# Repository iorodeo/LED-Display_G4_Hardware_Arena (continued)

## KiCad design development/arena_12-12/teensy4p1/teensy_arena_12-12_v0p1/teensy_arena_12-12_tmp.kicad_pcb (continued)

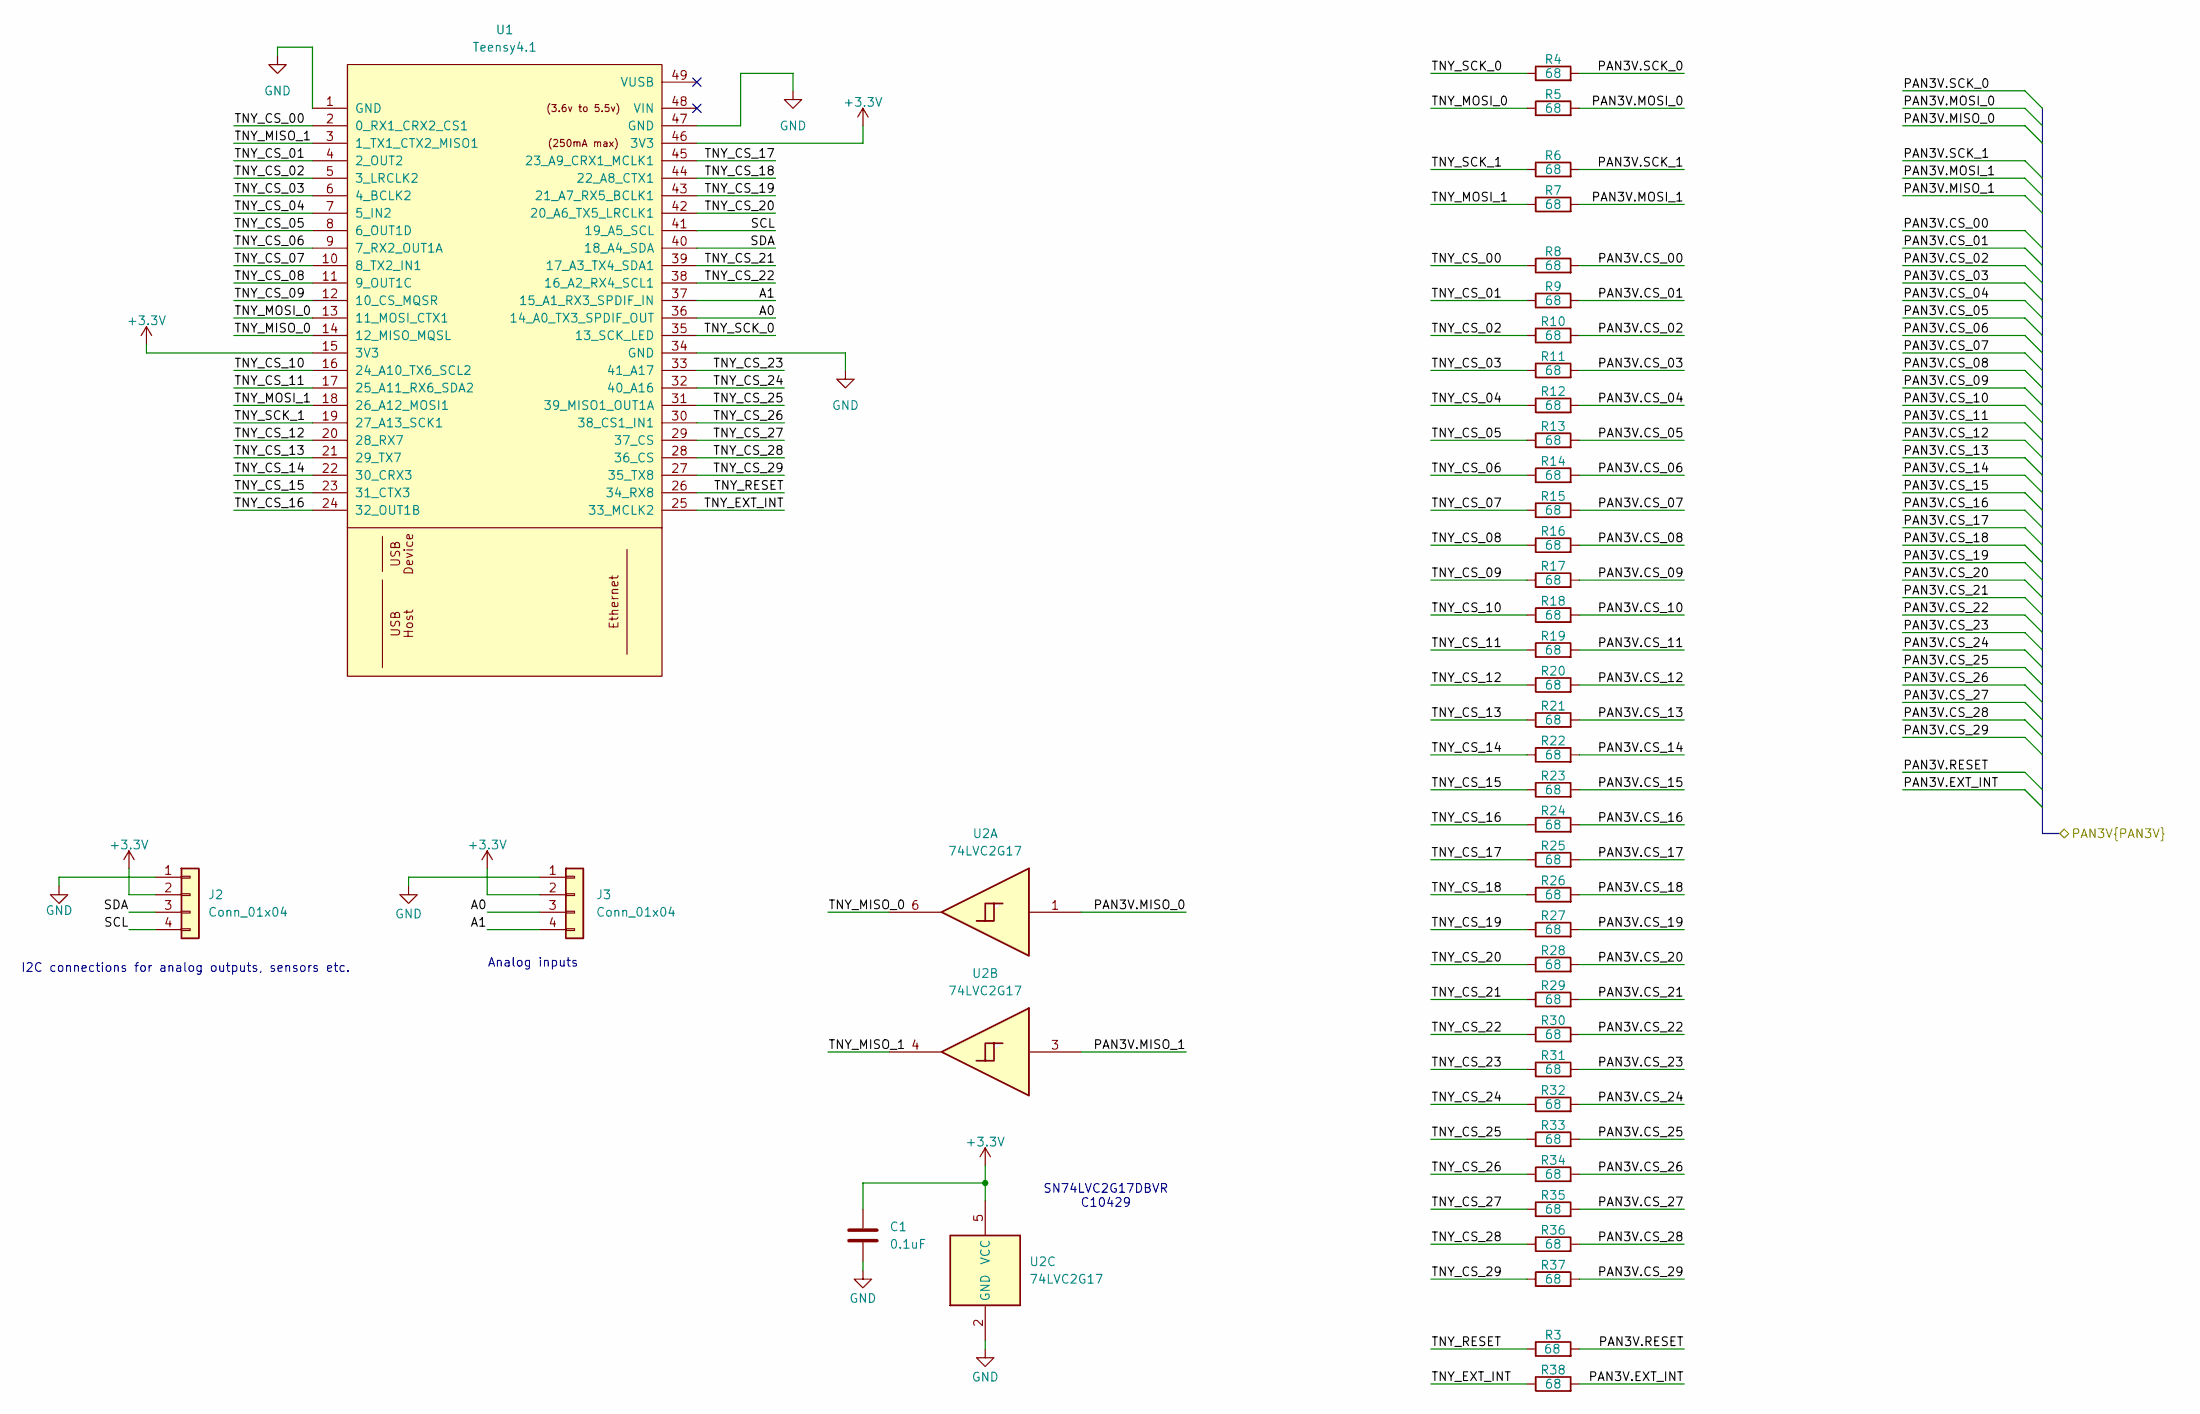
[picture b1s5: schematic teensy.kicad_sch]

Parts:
C1: 0.1uF; C_0402_1005Metric
J2, J3: Conn_01x04; JST_SH_SM04B-SRSS-TB_1x04-1MP_P1.00mm_Horizontal
R3, R4, R5, R6, R7, R8, R9, R10, R11, R12, R13, R14, R15, R16, R17, R18, R19, R20, R21, R22, R23, R24, R25, R26, R27, R28, R29, R30, R31, R32, R33, R34, R35, R36, R37, R38: 68; R_0402_1005Metric
U1: Teensy4.1; Teensy41_outer_only
U2: 74LVC2G17; SOT-23-6

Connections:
+3.3V: C1.1, J2.2, J3.2, U1.15 (3V3), U1.46 (3V3), U2.5 (VCC); also elsewhere on the board
/Level Shifters/PAN3V.CS_00: R8.2; also elsewhere on the board
/Level Shifters/PAN3V.CS_01: R9.2; also elsewhere on the board
/Level Shifters/PAN3V.CS_02: R10.2; also elsewhere on the board
/Level Shifters/PAN3V.CS_03: R11.2; also elsewhere on the board
/Level Shifters/PAN3V.CS_04: R12.2; also elsewhere on the board
/Level Shifters/PAN3V.CS_05: R13.2; also elsewhere on the board
/Level Shifters/PAN3V.CS_06: R14.2; also elsewhere on the board
/Level Shifters/PAN3V.CS_07: R15.2; also elsewhere on the board
/Level Shifters/PAN3V.CS_08: R16.2; also elsewhere on the board
/Level Shifters/PAN3V.CS_09: R17.2; also elsewhere on the board
/Level Shifters/PAN3V.CS_10: R18.2; also elsewhere on the board
/Level Shifters/PAN3V.CS_11: R19.2; also elsewhere on the board
/Level Shifters/PAN3V.CS_12: R20.2; also elsewhere on the board
/Level Shifters/PAN3V.CS_13: R21.2; also elsewhere on the board
/Level Shifters/PAN3V.CS_14: R22.2; also elsewhere on the board
/Level Shifters/PAN3V.CS_15: R23.2; also elsewhere on the board
/Level Shifters/PAN3V.CS_16: R24.2; also elsewhere on the board
/Level Shifters/PAN3V.CS_17: R25.2; also elsewhere on the board
/Level Shifters/PAN3V.CS_18: R26.2; also elsewhere on the board
/Level Shifters/PAN3V.CS_19: R27.2; also elsewhere on the board
/Level Shifters/PAN3V.CS_20: R28.2; also elsewhere on the board
/Level Shifters/PAN3V.CS_21: R29.2; also elsewhere on the board
/Level Shifters/PAN3V.CS_22: R30.2; also elsewhere on the board
/Level Shifters/PAN3V.CS_23: R31.2; also elsewhere on the board
/Level Shifters/PAN3V.CS_24: R32.2; also elsewhere on the board
/Level Shifters/PAN3V.CS_25: R33.2; also elsewhere on the board
/Level Shifters/PAN3V.CS_26: R34.2; also elsewhere on the board
/Level Shifters/PAN3V.CS_27: R35.2; also elsewhere on the board
/Level Shifters/PAN3V.CS_28: R36.2; also elsewhere on the board
/Level Shifters/PAN3V.CS_29: R37.2; also elsewhere on the board
/Level Shifters/PAN3V.EXT_INT: R38.2; also elsewhere on the board
/Level Shifters/PAN3V.MISO_0: U2.1; also elsewhere on the board
/Level Shifters/PAN3V.MISO_1: U2.3; also elsewhere on the board
/Level Shifters/PAN3V.MOSI_0: R5.2; also elsewhere on the board
/Level Shifters/PAN3V.MOSI_1: R7.2; also elsewhere on the board
/Level Shifters/PAN3V.RESET: R3.2; also elsewhere on the board
/Level Shifters/PAN3V.SCK_0: R4.2; also elsewhere on the board
/Level Shifters/PAN3V.SCK_1: R6.2; also elsewhere on the board
/Teensy/A0: J3.3, U1.36 (14_A0_TX3_SPDIF_OUT)
/Teensy/A1: J3.4, U1.37 (15_A1_RX3_SPDIF_IN)
/Teensy/SCL: J2.4, U1.41 (19_A5_SCL)
/Teensy/SDA: J2.3, U1.40 (18_A4_SDA)
/Teensy/TNY_CS_00: R8.1, U1.2 (0_RX1_CRX2_CS1)
/Teensy/TNY_CS_01: R9.1, U1.4 (2_OUT2)
/Teensy/TNY_CS_02: R10.1, U1.5 (3_LRCLK2)
/Teensy/TNY_CS_03: R11.1, U1.6 (4_BCLK2)
/Teensy/TNY_CS_04: R12.1, U1.7 (5_IN2)
/Teensy/TNY_CS_05: R13.1, U1.8 (6_OUT1D)
/Teensy/TNY_CS_06: R14.1, U1.9 (7_RX2_OUT1A)
/Teensy/TNY_CS_07: R15.1, U1.10 (8_TX2_IN1)
/Teensy/TNY_CS_08: R16.1, U1.11 (9_OUT1C)
/Teensy/TNY_CS_09: R17.1, U1.12 (10_CS_MQSR)
/Teensy/TNY_CS_10: R18.1, U1.16 (24_A10_TX6_SCL2)
/Teensy/TNY_CS_11: R19.1, U1.17 (25_A11_RX6_SDA2)
/Teensy/TNY_CS_12: R20.1, U1.20 (28_RX7)
/Teensy/TNY_CS_13: R21.1, U1.21 (29_TX7)
/Teensy/TNY_CS_14: R22.1, U1.22 (30_CRX3)
/Teensy/TNY_CS_15: R23.1, U1.23 (31_CTX3)
/Teensy/TNY_CS_16: R24.1, U1.24 (32_OUT1B)
/Teensy/TNY_CS_17: R25.1, U1.45 (23_A9_CRX1_MCLK1)
/Teensy/TNY_CS_18: R26.1, U1.44 (22_A8_CTX1)
/Teensy/TNY_CS_19: R27.1, U1.43 (21_A7_RX5_BCLK1)
/Teensy/TNY_CS_20: R28.1, U1.42 (20_A6_TX5_LRCLK1)
/Teensy/TNY_CS_21: R29.1, U1.39 (17_A3_TX4_SDA1)
/Teensy/TNY_CS_22: R30.1, U1.38 (16_A2_RX4_SCL1)
/Teensy/TNY_CS_23: R31.1, U1.33 (41_A17)
/Teensy/TNY_CS_24: R32.1, U1.32 (40_A16)
/Teensy/TNY_CS_25: R33.1, U1.31 (39_MISO1_OUT1A)
/Teensy/TNY_CS_26: R34.1, U1.30 (38_CS1_IN1)
/Teensy/TNY_CS_27: R35.1, U1.29 (37_CS)
/Teensy/TNY_CS_28: R36.1, U1.28 (36_CS)
/Teensy/TNY_CS_29: R37.1, U1.27 (35_TX8)
/Teensy/TNY_EXT_INT: R38.1, U1.25 (33_MCLK2)
/Teensy/TNY_MISO_0: U1.14 (12_MISO_MQSL), U2.6
/Teensy/TNY_MISO_1: U1.3 (1_TX1_CTX2_MISO1), U2.4
/Teensy/TNY_MOSI_0: R5.1, U1.13 (11_MOSI_CTX1)
/Teensy/TNY_MOSI_1: R7.1, U1.18 (26_A12_MOSI1)
/Teensy/TNY_RESET: R3.1, U1.26 (34_RX8)
/Teensy/TNY_SCK_0: R4.1, U1.35 (13_SCK_LED)
/Teensy/TNY_SCK_1: R6.1, U1.19 (27_A13_SCK1)
GND: C1.2, J2.1, J3.1, U1.1 (GND), U1.34 (GND), U1.47 (GND), U2.2 (GND); also elsewhere on the board

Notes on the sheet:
Analog inputs
I2C connections for analog outputs, sensors etc.
SN74LVC2G17DBVR C10429

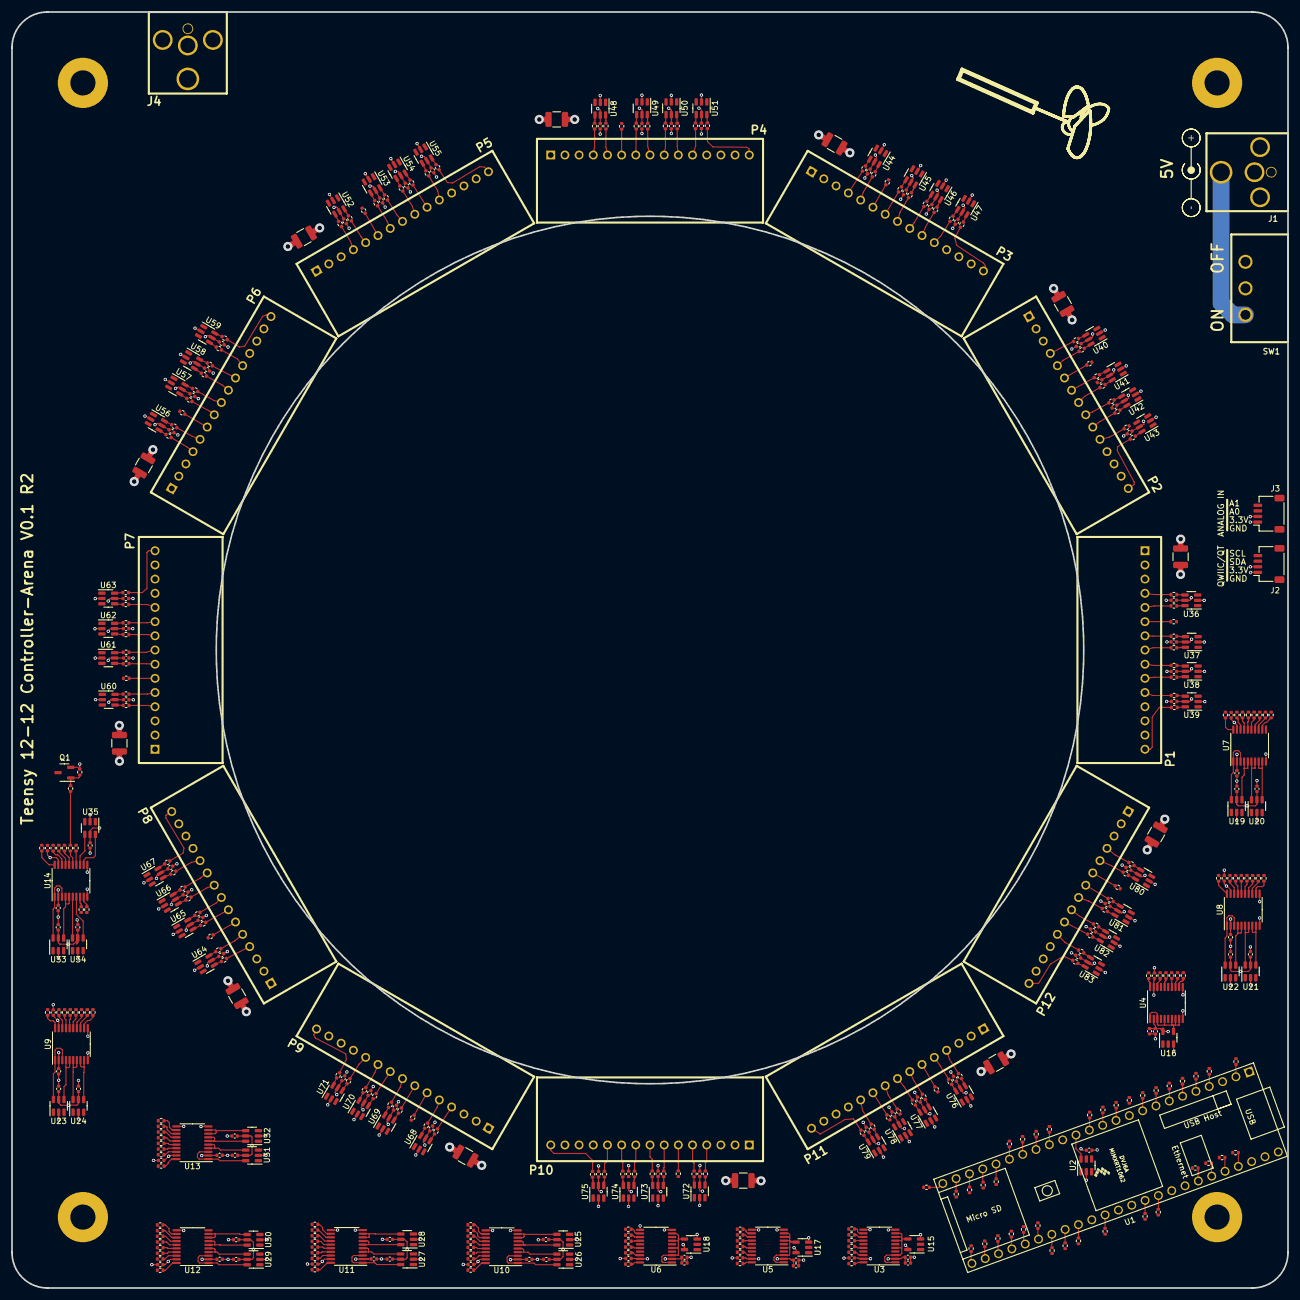
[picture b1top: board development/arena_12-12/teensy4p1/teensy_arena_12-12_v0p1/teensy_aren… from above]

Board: 6 copper layers, 228.6 x 228.6 mm, 445 parts (0 on the bottom side), 504 nets.

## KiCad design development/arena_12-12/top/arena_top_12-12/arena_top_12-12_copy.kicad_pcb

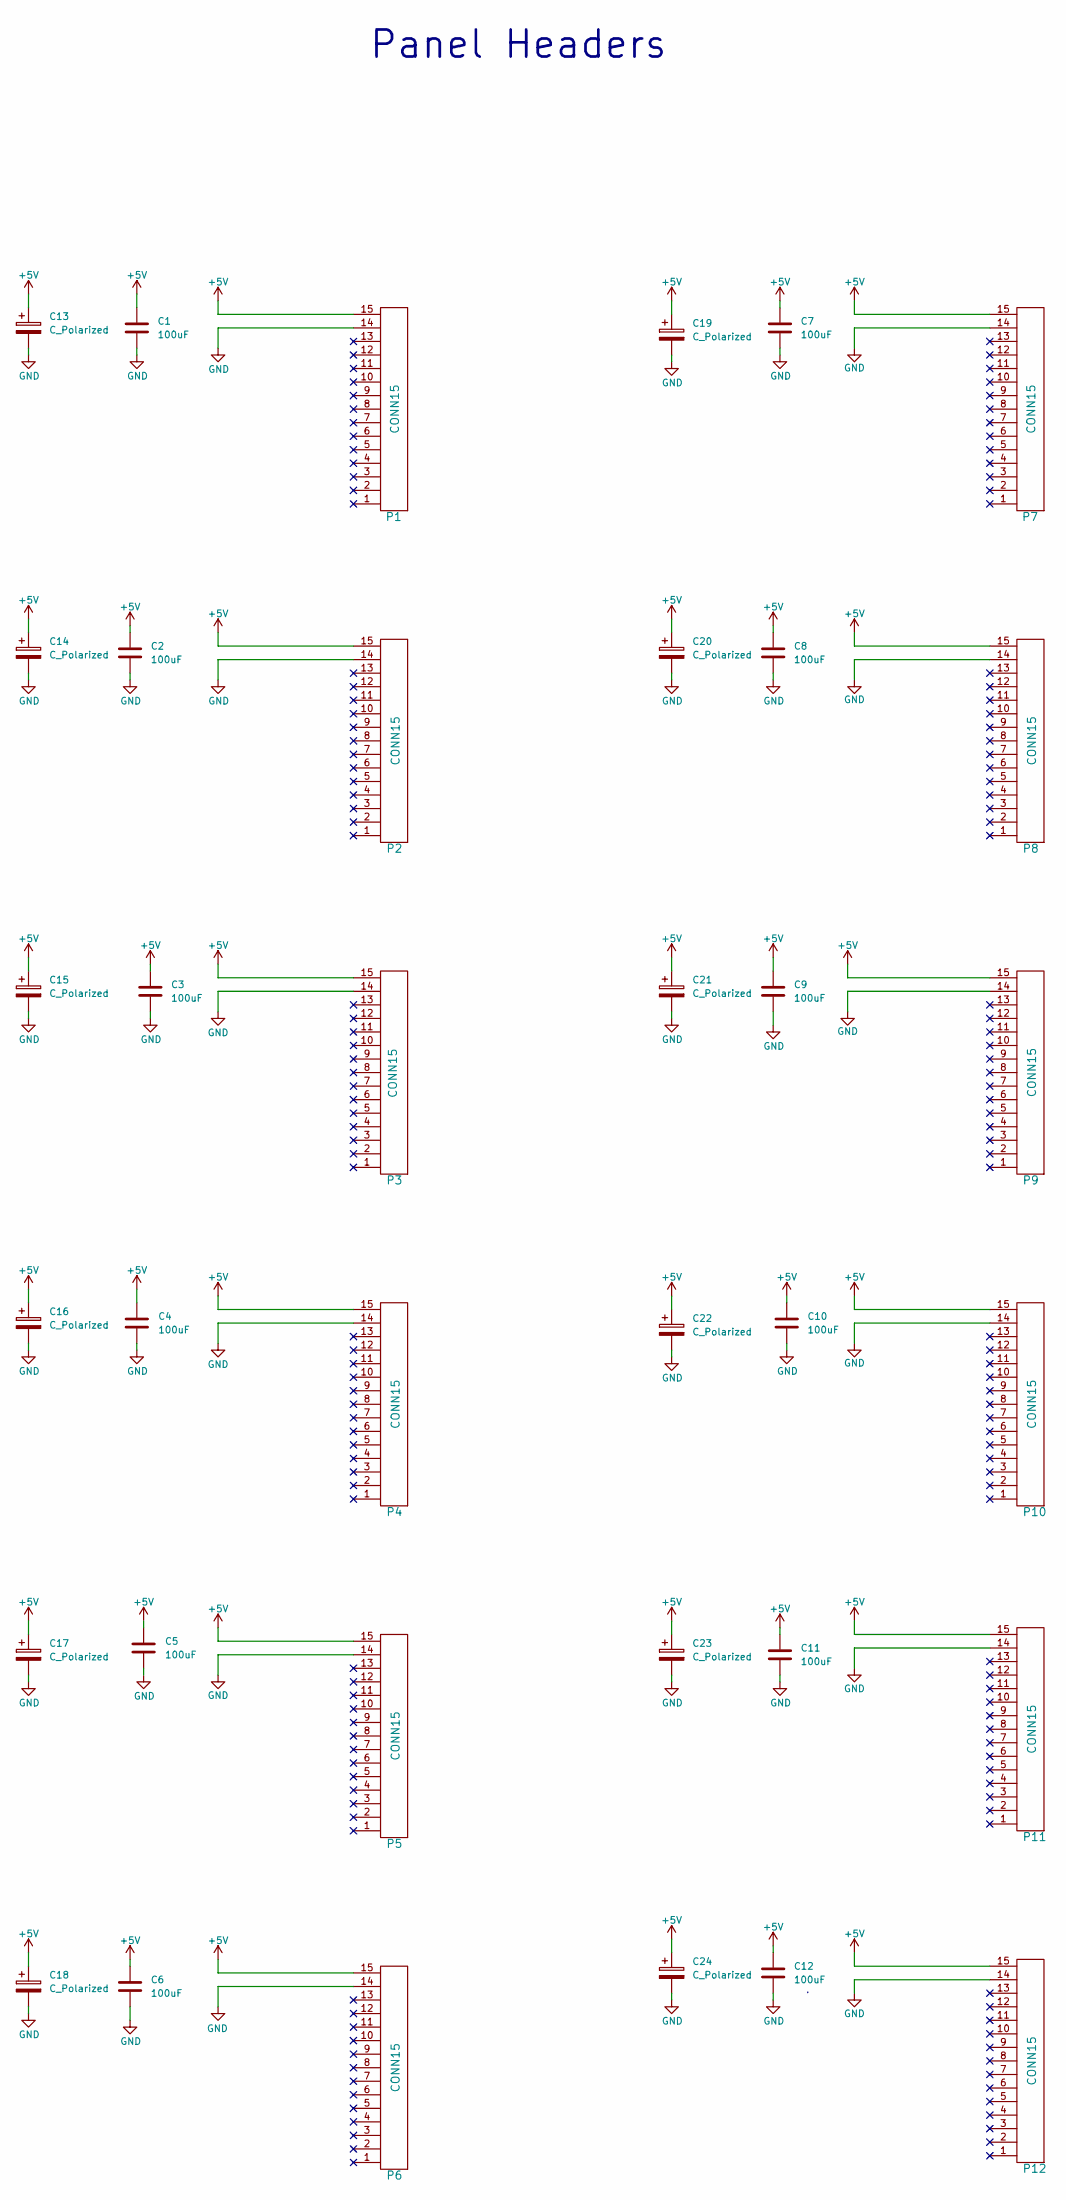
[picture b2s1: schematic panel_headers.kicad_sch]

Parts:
C1, C2, C3, C4, C5, C6, C7, C8, C9, C10, C11, C12: 100uF; C_1210_3225Metric
C13, C14, C15, C16, C17, C18, C19, C20, C21, C22, C23, C24: C_Polarized; CP_Radial_D8.0mm_P2.50mm
P1, P2, P3, P4, P5, P6, P7, P8, P9, P10, P11, P12: CONN15; HEADER_TOP

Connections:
+5V: C1.1, C2.1, C3.1, C4.1, C5.1, C6.1, C7.1, C8.1, C9.1, C10.1, C11.1, C12.1, C13.1, C14.1, C15.1, C16.1, C17.1, C18.1, C19.1, C20.1, C21.1, C22.1, C23.1, C24.1, P1.15, P2.15, P3.15, P4.15, P5.15, P6.15, P7.15, P8.15, P9.15, P10.15, P11.15, P12.15; also elsewhere on the board
GND: C1.2, C2.2, C3.2, C4.2, C5.2, C6.2, C7.2, C8.2, C9.2, C10.2, C11.2, C12.2, C13.2, C14.2, C15.2, C16.2, C17.2, C18.2, C19.2, C20.2, C21.2, C22.2, C23.2, C24.2, P1.14, P2.14, P3.14, P4.14, P5.14, P6.14, P7.14, P8.14, P9.14, P10.14, P11.14, P12.14; also elsewhere on the board

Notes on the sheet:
Panel Headers

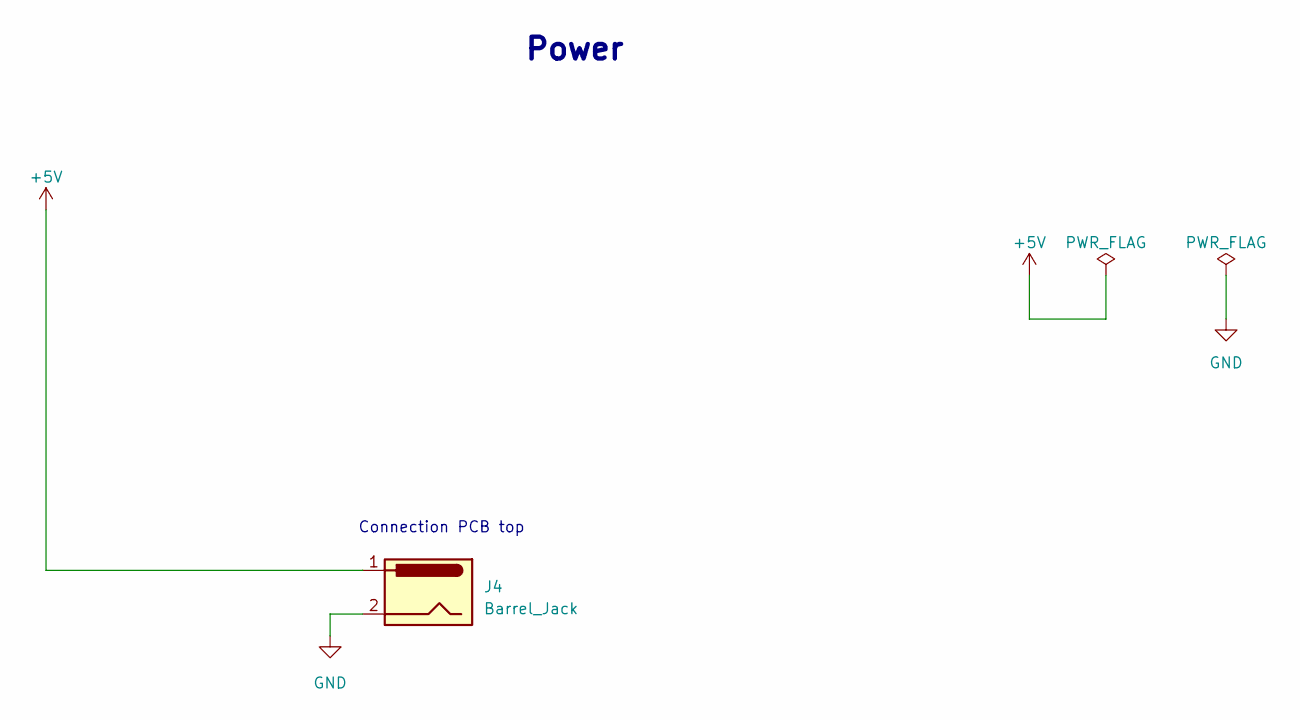
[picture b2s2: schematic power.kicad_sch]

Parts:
J4: Barrel_Jack; DCJACK_2PIN_HIGHCURRENT

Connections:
+5V: J4.1; also elsewhere on the board
GND: J4.2; also elsewhere on the board

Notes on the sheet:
Connection PCB top
Power

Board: 6 copper layers, 41 parts (0 on the bottom side), 2 nets, no tracks yet.

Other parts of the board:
H1, H2, H3, H4: MountingHole_Pad; MountingHole_4.5mm_Pad

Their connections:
GND: H1.1, H2.1, H3.1, H4.1; also elsewhere on the board

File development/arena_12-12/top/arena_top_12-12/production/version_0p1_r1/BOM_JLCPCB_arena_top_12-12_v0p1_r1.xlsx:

Comment | Designator | Footprint | LCSC Part | Qty
100uF ceramic Capacitor | C3,C4,C12,C8,C5,C11,C1,C2,C6,C10,C9,C7 | 1210 | C7432790 | 12
100uF Electrolytic Capacitor | C16,C24,C23,C19,C21,C22,C14,C18,C17,C20,C15,C13 | CP_Radial_D8.0mm_P2.50mm | global parts | 12
DC Power Barrel Jack | J1 | through hole | global parts | 1
15x1 male header, 0.1in pitch | P1,P2,P3,P4,P5,P6,P7,P8,P9,P10,P11,P12 | through hole | global parts | 12

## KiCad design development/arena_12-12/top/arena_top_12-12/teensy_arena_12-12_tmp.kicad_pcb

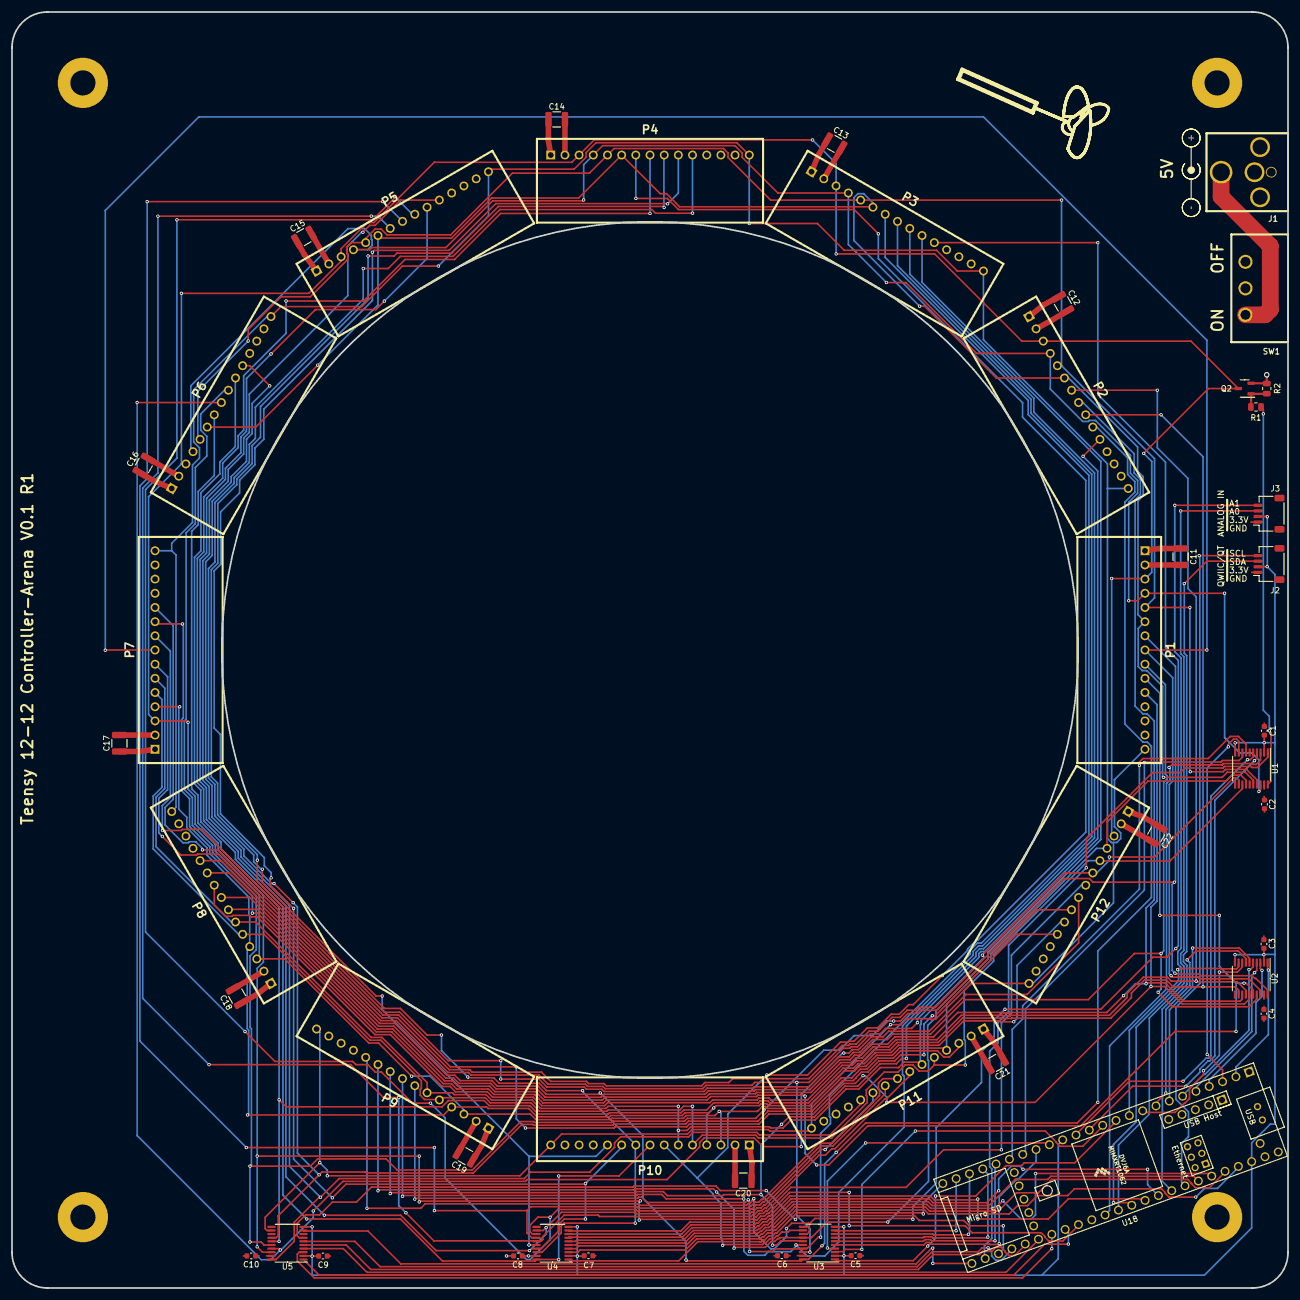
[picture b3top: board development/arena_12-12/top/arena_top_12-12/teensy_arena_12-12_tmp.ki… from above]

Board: 4 copper layers, 228.6 x 228.6 mm, 51 parts (0 on the bottom side), 86 nets.

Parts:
C1, C2, C3, C4, C5, C6, C7, C8, C9, C10: 0.1uF; C_0603_1608Metric
C11, C12, C13, C14, C15, C16, C17, C18, C19, C20, C21, C22: 100uF; C_1210_3225Metric
H1, H2, H3, H4: MountingHole_Pad; MountingHole_4.5mm_Pad
J1: Barrel_Jack; DCJACK_2PIN_HIGHCURRENT
J2, J3: Conn_01x04; JST_SH_SM04B-SRSS-TB_1x04-1MP_P1.00mm_Horizontal
P1, P2, P3, P4, P5, P6, P7, P8, P9, P10, P11, P12: CONN15; HEADER_TOP
Q2: MOSFET_NCHAN; SOT-23-3
R1: 200; R_0805_2012Metric
R2: 20k; R_0805_2012Metric
SW1: SW_SPDT; slide_switch
U1, U2, U3, U4, U5: TXB0108PW; TSSOP-20_4.4x6.5mm_P0.65mm
U18: Teensy4.1; Teensy41

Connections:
+3.3V: C1.1, C3.1, C5.1, C7.1, C9.1, J2.2, J3.2, U1.2 (VCCA), U1.10 (OE), U2.2 (VCCA), U2.10 (OE), U3.2 (VCCA), U3.10 (OE), U4.2 (VCCA), U4.10 (OE), U5.2 (VCCA), U5.10 (OE), U18.15 (3V3), U18.46 (3V3)
+5V: C2.1, C4.1, C6.1, C8.1, C10.1, C11.1, C12.1, C13.1, C14.1, C15.1, C16.1, C17.1, C18.1, C19.1, C20.1, C21.1, C22.1, P1.1, P2.1, P3.1, P4.1, P5.1, P6.1, P7.1, P8.1, P9.1, P10.1, P11.1, P12.1, SW1.2 (B), U1.19 (VCCB), U2.19 (VCCB), U3.19 (VCCB), U4.19 (VCCB), U5.19 (VCCB)
/Level Shifters/PAN3V.CS_00: U2.1 (A1), U18.2 (0_RX1_CRX2_CS1)
/Level Shifters/PAN3V.CS_01: U2.3 (A2), U18.4 (2_OUT2)
/Level Shifters/PAN3V.CS_02: U2.4 (A3), U18.5 (3_LRCLK2)
/Level Shifters/PAN3V.CS_03: U2.5 (A4), U18.6 (4_BCLK2)
/Level Shifters/PAN3V.CS_04: U2.6 (A5), U18.7 (5_IN2)
/Level Shifters/PAN3V.CS_05: U2.7 (A6), U18.8 (6_OUT1D)
/Level Shifters/PAN3V.CS_06: U2.8 (A7), U18.9 (7_RX2_OUT1A)
/Level Shifters/PAN3V.CS_07: U2.9 (A8), U18.10 (8_TX2_IN1)
/Level Shifters/PAN3V.CS_08: U3.1 (A1), U18.11 (9_OUT1C)
/Level Shifters/PAN3V.CS_09: U3.3 (A2), U18.12 (10_CS_MQSR)
/Level Shifters/PAN3V.CS_10: U3.4 (A3), U18.16 (24_A10_TX6_SCL2)
/Level Shifters/PAN3V.CS_11: U3.5 (A4), U18.17 (25_A11_RX6_SDA2)
/Level Shifters/PAN3V.CS_12: U3.6 (A5), U18.20 (28_RX7)
/Level Shifters/PAN3V.CS_13: U3.7 (A6), U18.21 (29_TX7)
/Level Shifters/PAN3V.CS_14: U3.8 (A7), U18.22 (30_CRX3)
/Level Shifters/PAN3V.CS_15: U3.9 (A8), U18.23 (31_CTX3)
/Level Shifters/PAN3V.CS_16: U4.1 (A1), U18.24 (32_OUT1B)
/Level Shifters/PAN3V.CS_17: U4.3 (A2), U18.45 (23_A9_CRX1_MCLK1)
/Level Shifters/PAN3V.CS_18: U4.4 (A3), U18.44 (22_A8_CTX1)
/Level Shifters/PAN3V.CS_19: U4.5 (A4), U18.43 (21_A7_RX5_BCLK1)
/Level Shifters/PAN3V.CS_20: U4.6 (A5), U18.42 (20_A6_TX5_LRCLK1)
/Level Shifters/PAN3V.CS_21: U4.7 (A6), U18.39 (17_A3_TX4_SDA1)
/Level Shifters/PAN3V.CS_22: U4.8 (A7), U18.38 (16_A2_RX4_SCL1)
/Level Shifters/PAN3V.CS_23: U4.9 (A8), U18.33 (41_A17)
/Level Shifters/PAN3V.CS_24: U5.1 (A1), U18.32 (40_A16)
/Level Shifters/PAN3V.CS_25: U5.3 (A2), U18.31 (39_MISO1_OUT1A)
/Level Shifters/PAN3V.CS_26: U5.4 (A3), U18.30 (38_CS1_IN1)
/Level Shifters/PAN3V.CS_27: U5.5 (A4), U18.29 (37_CS)
/Level Shifters/PAN3V.CS_28: U5.6 (A5), U18.28 (36_CS)
/Level Shifters/PAN3V.CS_29: U5.7 (A6), U18.27 (35_TX8)
/Level Shifters/PAN3V.EXT_INT: U5.9 (A8), U18.25 (33_MCLK2)
/Level Shifters/PAN3V.MISO_0: U1.5 (A4), U18.14 (12_MISO_MQSL)
/Level Shifters/PAN3V.MISO_1: U1.9 (A8), U18.3 (1_TX1_CTX2_MISO1)
/Level Shifters/PAN3V.MOSI_0: U1.4 (A3), U18.13 (11_MOSI_CTX1)
/Level Shifters/PAN3V.MOSI_1: U1.8 (A7), U18.18 (26_A12_MOSI1)
/Level Shifters/PAN3V.RESET: U1.1 (A1), U18.26 (34_RX8)
/Level Shifters/PAN3V.SCK_0: U1.3 (A2), U18.35 (13_SCK_LED)
/Level Shifters/PAN3V.SCK_1: U1.7 (A6), U18.19 (27_A13_SCK1)
/Level Shifters/PAN5V.CS_00: P1.7, P7.7, U2.20 (B1)
/Level Shifters/PAN5V.CS_01: P1.8, P7.8, U2.18 (B2)
/Level Shifters/PAN5V.CS_02: P1.9, P7.9, U2.17 (B3)
/Level Shifters/PAN5V.CS_03: P1.10, P7.10, U2.16 (B4)
/Level Shifters/PAN5V.CS_04: P1.11, P7.11, U2.15 (B5)
/Level Shifters/PAN5V.CS_05: P2.7, P8.7, U2.14 (B6)
/Level Shifters/PAN5V.CS_06: P2.8, P8.8, U2.13 (B7)
/Level Shifters/PAN5V.CS_07: P2.9, P8.9, U2.12 (B8)
/Level Shifters/PAN5V.CS_08: P2.10, P8.10, U3.20 (B1)
/Level Shifters/PAN5V.CS_09: P2.11, P8.11, U3.18 (B2)
/Level Shifters/PAN5V.CS_10: P3.7, P9.7, U3.17 (B3)
/Level Shifters/PAN5V.CS_11: P3.8, P9.8, U3.16 (B4)
/Level Shifters/PAN5V.CS_12: P3.9, P9.9, U3.15 (B5)
/Level Shifters/PAN5V.CS_13: P3.10, P9.10, U3.14 (B6)
/Level Shifters/PAN5V.CS_14: P3.11, P9.11, U3.13 (B7)
/Level Shifters/PAN5V.CS_15: P4.7, P10.7, U3.12 (B8)
/Level Shifters/PAN5V.CS_16: P4.8, P10.8, U4.20 (B1)
/Level Shifters/PAN5V.CS_17: P4.9, P10.9, U4.18 (B2)
/Level Shifters/PAN5V.CS_18: P4.10, P10.10, U4.17 (B3)
/Level Shifters/PAN5V.CS_19: P4.11, P10.11, U4.16 (B4)
/Level Shifters/PAN5V.CS_20: P5.7, P11.7, U4.15 (B5)
/Level Shifters/PAN5V.CS_21: P5.8, P11.8, U4.14 (B6)
/Level Shifters/PAN5V.CS_22: P5.9, P11.9, U4.13 (B7)
/Level Shifters/PAN5V.CS_23: P5.10, P11.10, U4.12 (B8)
/Level Shifters/PAN5V.CS_24: P5.11, P11.11, U5.20 (B1)
/Level Shifters/PAN5V.CS_25: P6.7, P12.7, U5.18 (B2)
/Level Shifters/PAN5V.CS_26: P6.8, P12.8, U5.17 (B3)
/Level Shifters/PAN5V.CS_27: P6.9, P12.9, U5.16 (B4)
/Level Shifters/PAN5V.CS_28: P6.10, P12.10, U5.15 (B5)
/Level Shifters/PAN5V.CS_29: P6.11, P12.11, U5.14 (B6)
/Level Shifters/PAN5V.EXT_INT: P1.15, P2.15, P3.15, P4.15, P5.15, P6.15, P7.15, P8.15, P9.15, P10.15, P11.15, P12.15, U5.12 (B8)
/Level Shifters/PAN5V.MISO_0: P1.6, P2.6, P3.6, P4.6, P5.6, P6.6, U1.16 (B4)
/Level Shifters/PAN5V.MISO_1: P7.6, P8.6, P9.6, P10.6, P11.6, P12.6, U1.12 (B8)
/Level Shifters/PAN5V.MOSI_0: P1.5, P2.5, P3.5, P4.5, P5.5, P6.5, U1.17 (B3)
/Level Shifters/PAN5V.MOSI_1: P7.5, P8.5, P9.5, P10.5, P11.5, P12.5, U1.13 (B7)
/Level Shifters/PAN5V.RESET: R1.2, U1.20 (B1)
/Level Shifters/PAN5V.SCK_0: P1.4, P2.4, P3.4, P4.4, P5.4, P6.4, U1.18 (B2)
/Level Shifters/PAN5V.SCK_1: P7.4, P8.4, P9.4, P10.4, P11.4, P12.4, U1.14 (B6)
/Panel Headers/RESET: P1.3, P2.3, P3.3, P4.3, P5.3, P6.3, P7.3, P8.3, P9.3, P10.3, P11.3, P12.3, Q2.3 (D)
/Power/SW_5V: J1.1, SW1.1 (A)
/Teensy/A0: J3.3, U18.36 (14_A0_TX3_SPDIF_OUT)
/Teensy/A1: J3.4, U18.37 (15_A1_RX3_SPDIF_IN)
/Teensy/SCL: J2.4, U18.41 (19_A5_SCL)
/Teensy/SDA: J2.3, U18.40 (18_A4_SDA)
GND: C1.2, C2.2, C3.2, C4.2, C5.2, C6.2, C7.2, C8.2, C9.2, C10.2, C11.2, C12.2, C13.2, C14.2, C15.2, C16.2, C17.2, C18.2, C19.2, C20.2, C21.2, C22.2, H1.1, H2.1, H3.1, H4.1, J1.2, J2.1, J3.1, P1.2, P2.2, P3.2, P4.2, P5.2, P6.2, P7.2, P8.2, P9.2, P10.2, P11.2, P12.2, Q2.2 (S), R2.1, SW1.3 (C), U1.11 (GND), U2.11 (GND), U3.11 (GND), U4.11 (GND), U5.11 (GND), U18.1 (GND), U18.34 (GND), U18.47 (GND)
unnamed: Q2.1 (G), R1.1, R2.2
